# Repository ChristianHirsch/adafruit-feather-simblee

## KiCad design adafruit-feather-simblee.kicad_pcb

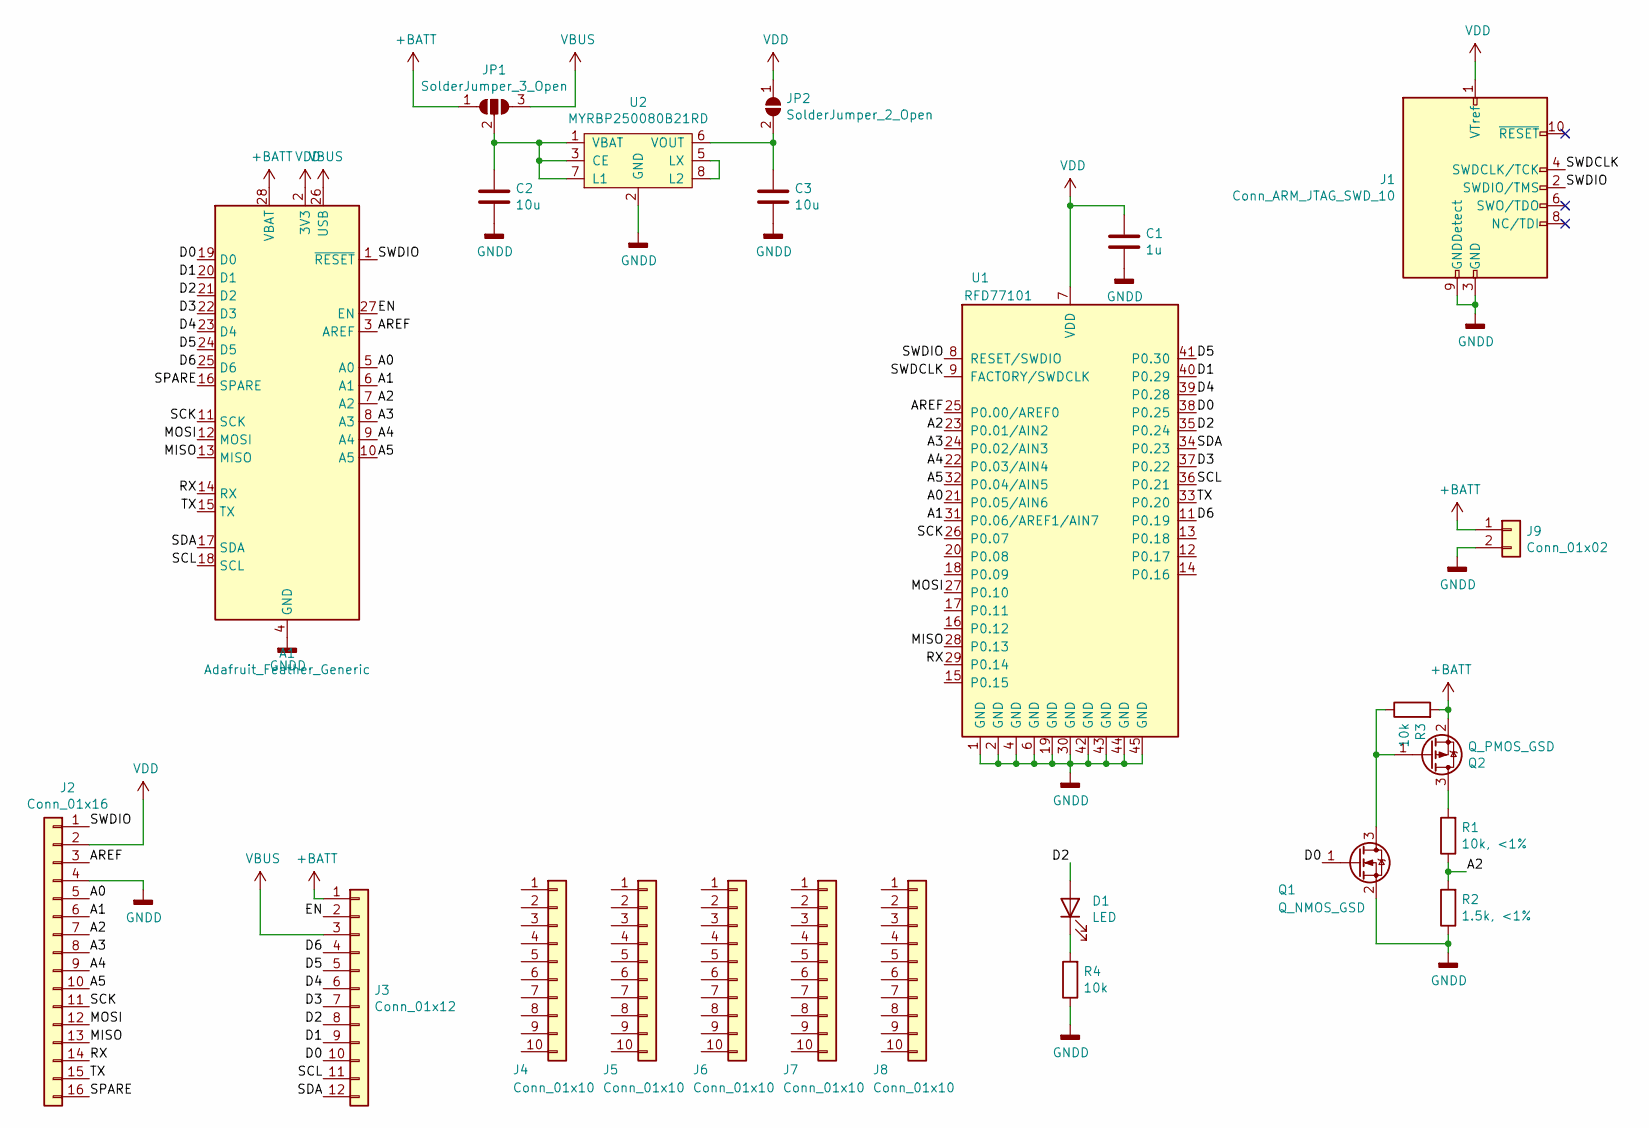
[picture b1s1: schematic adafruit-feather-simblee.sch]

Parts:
A1: Adafruit_Feather_Generic; Adafruit_Feather_WithMountingHoles
C1: 1u; C_0805_2012Metric
C2, C3: 10u; C_0805_2012Metric
D1: LED; LED_0603_1608Metric
J1: Conn_ARM_JTAG_SWD_10; PinHeader_2x05_P1.27mm_Vertical_SMD
J2: Conn_01x16; PinHeader_1x16_P2.54mm_Vertical
J3: Conn_01x12; PinHeader_1x12_P2.54mm_Vertical
J4, J5, J6, J7, J8: Conn_01x10; PinSocket_1x10_P2.54mm_Vertical
J9: Conn_01x02; JST_PH_S2B-PH-K_1x02_P2.00mm_Horizontal
JP1: SolderJumper_3_Open; SolderJumper-3_P1.3mm_Open_RoundedPad1.0x1.5mm
JP2: SolderJumper_2_Open; SolderJumper-2_P1.3mm_Open_RoundedPad1.0x1.5mm
Q1: Q_NMOS_GSD; SOT-23
Q2: Q_PMOS_GSD; SOT-23
R1: 10k, <1%; R_0402_1005Metric
R2: 1.5k, <1%; R_0402_1005Metric
R3, R4: 10k; R_0402_1005Metric
U1: RFD77101; RFDigital_RFD77101
U2: MYRBP250080B21RD; MYRBP

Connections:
+BATT: A1.28 (VBAT), J3.1, J9.1, JP1.1 (A), Q2.2 (S), R3.2
/A0: A1.5 (A0), J2.5, U1.21 (P0.05/AIN6)
/A1: A1.6 (A1), J2.6, U1.31 (P0.06/AREF1/AIN7)
/A2: A1.7 (A2), J2.7, R1.1, R2.2, U1.23 (P0.01/AIN2)
/A3: A1.8 (A3), J2.8, U1.24 (P0.02/AIN3)
/A4: A1.9 (A4), J2.9, U1.22 (P0.03/AIN4)
/A5: A1.10 (A5), J2.10, U1.32 (P0.04/AIN5)
/AREF: A1.3 (AREF), J2.3, U1.25 (P0.00/AREF0)
/D0: A1.19 (D0), J3.10, Q1.1 (G), U1.38 (P0.25)
/D1: A1.20 (D1), J3.9, U1.40 (P0.29)
/D2: A1.21 (D2), D1.2 (A), J3.8, U1.35 (P0.24)
/D3: A1.22 (D3), J3.7, U1.37 (P0.22)
/D4: A1.23 (D4), J3.6, U1.39 (P0.28)
/D5: A1.24 (D5), J3.5, U1.41 (P0.30)
/D6: A1.25 (D6), J3.4, U1.11 (P0.19)
/EN: A1.27 (EN), J3.2
/MISO: A1.13 (MISO), J2.13, U1.28 (P0.13)
/MOSI: A1.12 (MOSI), J2.12, U1.27 (P0.10)
/RX: A1.14 (RX), J2.14, U1.29 (P0.14)
/SCK: A1.11 (SCK), J2.11, U1.26 (P0.07)
/SCL: A1.18 (SCL), J3.11, U1.36 (P0.21)
/SDA: A1.17 (SDA), J3.12, U1.34 (P0.23)
/SPARE: A1.16 (SPARE), J2.16
/SWDCLK: J1.4 (SWDCLK/TCK), U1.9 (FACTORY/SWDCLK)
/SWDIO: A1.1 (~RESET), J1.2 (SWDIO/TMS), J2.1, U1.8 (RESET/SWDIO)
/TX: A1.15 (TX), J2.15, U1.33 (P0.20)
GND: A1.4 (GND), C1.2, C2.2, C3.2, J1.3 (GND), J1.5 (GND), J1.9 (GNDDetect), J2.4, J9.2, Q1.2 (S), R2.1, R4.1, U1.1 (GND), U1.2 (GND), U1.4 (GND), U1.6 (GND), U1.19 (GND), U1.30 (GND), U1.42 (GND), U1.43 (GND), U1.44 (GND), U1.45 (GND), U2.2 (GND), U2.4 (GND), U2.EP
unnamed: C2.1, JP1.2 (C), U2.1 (VBAT), U2.3 (CE), U2.7 (L1)
unnamed: C3.1, JP2.2 (B), U2.6 (VOUT)
unnamed: D1.1 (K), R4.2
unnamed: Q1.3 (D), Q2.1 (G), R3.1
unnamed: Q2.3 (D), R1.2
unnamed: U2.5 (LX), U2.8 (L2)
VBUS: A1.26 (USB), J3.3, JP1.3 (B)
VDD: A1.2 (3V3), C1.1, J1.1 (VTref), J2.2, JP2.1 (A), U1.7 (VDD)

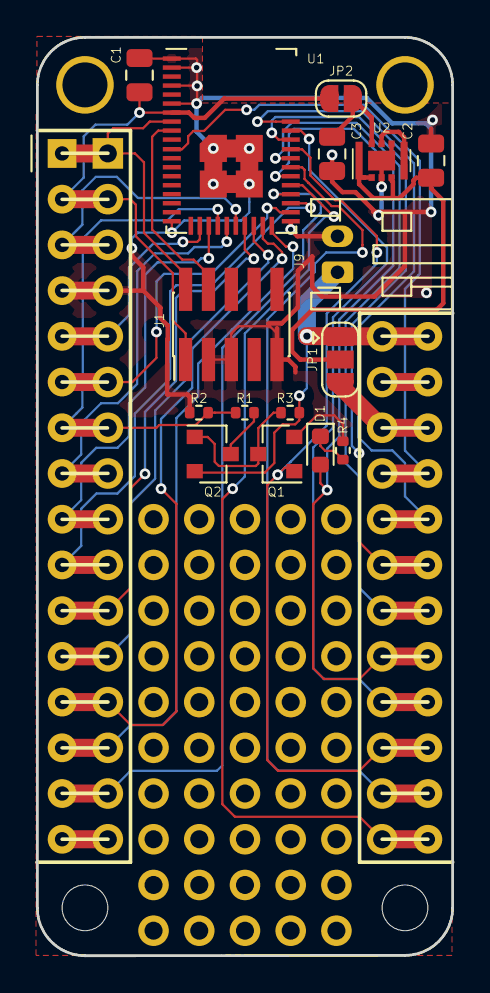
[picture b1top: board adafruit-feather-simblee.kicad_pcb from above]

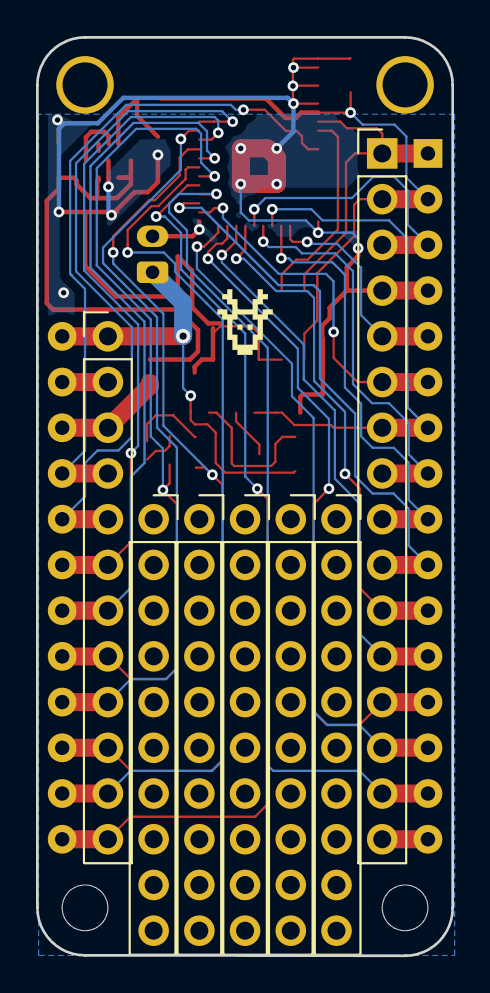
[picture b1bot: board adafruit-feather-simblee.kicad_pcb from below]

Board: 2 copper layers, 23.1 x 51.0 mm, 24 parts (7 on the bottom side), 35 nets.
